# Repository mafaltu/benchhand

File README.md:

<!-- SPDX-License-Identifier: CC-BY-SA-4.0 -->
<!-- Copyright (c) 2026 Martin Faltus (mafaltu) -->

<h1 align="center">BenchHand</h1>

<p align="center"><b>Remote hands for your test bench</b><br>
Press buttons, flip switches, power-cycle boards, unplug USB and read signals from a script, a CI job or an AI agent.</p>

<p align="center">

</p>

---

## What is it?

BenchHand is a small USB box that sits between your computer and the hardware you are developing. It gives the
computer what it has always lacked on a test bench: **hands and eyes**.

- **5 relays** (potential-free contacts NC / COM / NO) can do anything a hand or a switch would. They press any button
  on the device, stand in for a switch, power-cycle a small board, apply a voltage to an input, or set a jumper or strap
  pin. They are signal relays (1 A at up to 30 V DC), made for low-voltage bench signals, not for mains or heavy loads.
- **A switched USB 2.0 passthrough** (480 Mbit/s) unplugs and replugs a USB device or programmer in software, power and
  data, with no hand on the cable.
- **4 isolated digital inputs** (3-12 V) are the eyes. They watch an LED, an output pin, a status line or a power rail
  of the device under test, so you can check that it actually reacted.
- **Physical buttons and LEDs** let a human take over at any time.
- **One USB serial port** with a plain-text protocol works from any language, a shell script, a CI pipeline, or an AI
  agent that just types `HELP`.

## Why this exists

Hardware development has a dirty secret: the automation stops at the USB cable.

Your scripts can build, flash and test. Your CI can run all night. Your AI agent can debug firmware for hours. And then,
sooner or later, somebody has to **press a button**, **hold BOOT while plugging in USB**, **unplug the device and plug it
back in**, **flip a switch**, **power-cycle the target**, or **check whether that LED actually lit up**.

That somebody is a human. Humans aren't at the desk 24/7, don't answer in milliseconds, get bored of pressing the same
button for the 40th time, and occasionally go to sleep. So the whole automated pipeline sits and waits.

BenchHand removes the human from that loop, so automation can run all the way to the hardware.

## A taste of it

```text
> ID?
< OK model=BenchHand hw=r1 fw=0.1.0 proto=1 sn=005900A75943501420363441
> PULSE 1 200                         # press "reset" (relay 1) for 200 ms
< OK
> SEQ SET 2 ON; DELAY 50; SET 1 ON; DELAY 100; SET 1 OFF; DELAY 50; SET 2 OFF
< OK steps=7 delay_ms=200 async=0     # hold BOOT, tap RESET, release BOOT
> USB DISCONNECT 2000                 # unplug the USB device for 2 s, then plug it back in
< OK
> INPUT?
< OK in=0,0,0,0 rise=0,0,0,0 fall=0,0,0,0
```

What people do with it (the list is open, a relay contact plus an input can stand in for a lot):

| Use | How |
|---|---|
| **Press any button** | reset, boot, power, a menu key, a doorbell: a relay contact across the button |
| **Flip a switch** | anything that is just a contact: a door contact, a limit, reed or float switch, an on/off status line; or move an analog input between fixed points by switching resistors (e.g. a "cold" and a "hot" NTC value) |
| **Apply a signal** | switch a voltage onto an input of the device and check that the firmware notices |
| **Power-cycle** | restart a low-power board that hangs, or interrupt its supply to test brown-out recovery (signal relays: 1 A / 30 V DC max) |
| **Re-plug USB** | re-enumerate a device or programmer, test hot-plug handling, without touching the cable |
| **Watch the result** | read LEDs, output pins or rails on the isolated inputs, and count edges |
| **Close the loop** | flash an ESP32 / STM32 / RP2040, put it into its bootloader, reset it and verify it, unattended, from CI or an AI coding agent |

## Features

| | |
|---|---|
| **Control port** | USB-C, USB 2.0 Full Speed CDC ACM (no driver on Linux, macOS or Windows 10+) |
| **Relays** | 5 x SPDT (NC / COM / NO) on screw terminals, signal relays rated 1 A at up to 30 V DC (low-voltage use only, no mains), coil-state LED per relay |
| **USB passthrough** | USB-B in, USB-A out, USB 2.0 High Speed (tested at 480 Mbit/s), eFuse-protected VBUS with fault latch, software-switched data and power |
| **Inputs** | 4 x optically isolated, 3-12 V = HIGH, edge detection (`rise=` / `fall=`) |
| **Safety** | relays auto-release after `MAX_ON` (default 60 s), everything off on reset and on host sleep, watchdog |
| **Protocol** | text lines, exactly one `OK` / `ERR` reply per command, self-documenting `HELP`, sequences (`SEQ`) |
| **MCU** | STM32C071 (Cortex-M0+), crystal-less USB, firmware update over USB DFU |
| **Board** | 188.8 x 40 mm, 2 layers, all SMD on one side, designed for home assembly (stencil + hot plate / reflow) |
| **Enclosure** | 3D-printed, two parts, two-colour lid with labels (single colour works too) |

## How it works

<p align="center">
  <picture>
    <source media="(prefers-color-scheme: dark)" srcset="docs/images/block-diagram-dark.svg">
    
  </picture>
</p>

The hardware design is described in [hardware/docs](hardware/docs/README.md), and the reasons behind the main choices
are collected in [docs/design-decisions.md](docs/design-decisions.md).

## For AI agents

BenchHand is a USB device that gives a program hands on a test bench. It has 5 relays (dry contacts NC / COM / NO) to
press buttons or reset and power-cycle a device under test (DUT). It has 4 isolated digital inputs (3-12 V = HIGH) to
read DUT signals. And it has a switched USB 2.0 passthrough (USB-B in, USB-A out) to unplug and replug a programmer or
USB device. You control it with plain-text lines over a USB serial port (CDC ACM).

**Port.**
- Linux: `/dev/serial/by-id/usb-mafaltu_BenchHand_<serial>-if00`.
- macOS: `/dev/cu.usbmodem*` (not tested).
- Windows: a `COMn` port, USB ID `1209:0001` (not tested). Match on the name `BenchHand`, not on the PID.

If several boards are connected, ask the user which one to use, and match the `sn=` field of `ID?`.

**Open.**
- Linux shell: run `stty -F <port> raw -echo` first.
- Python: use `serial.Serial(port, timeout=1)`. Baud rate, parity and DTR / RTS are ignored.
- Only one program at a time. Use `flock <port> <cmd>` if several programs may open the port.

**Protocol.**
- One command per line (LF, CR or CRLF), at most 320 characters, case-insensitive, channels by number (relays 1-5,
  inputs 1-4).
- Exactly one reply per command, in order: zero or more data lines starting with `# `, then one final line starting
  with `OK` or `ERR`. Read until that final line.
- Errors look like `ERR <code> <reason>: <hint>`, and the hint says how to fix the call.
- `HELP` lists the commands, and `HELP <command>` gives details and examples.

**Rules you must respect.**
1. **Ask what is wired.** The board does not know what a relay or input is connected to. Ask the user (e.g. "relay 1 =
   DUT reset to GND, input 1 = status LED") and use only those channels.
2. **Relays switch real circuits.** Never switch a relay you were not told about. A relay switched ON from the port
   turns OFF by itself after `MAX_ON` (60 s by default). Send `SET <n> ON` again as a keep-alive. Change `MAX_ON` only
   if the user agrees.
3. **After a board reset everything is off**, except the USB passthrough, which comes back ON.
4. **Host sleep turns everything off.** So does Linux USB autosuspend while no program has the port open. Keep the
   port open or ask the user about the udev rule in the [firmware README](firmware/README.md).
5. **Unplugging through the passthrough is not a safe eject.** Unmount mass-storage devices first.
6. **`ext=1` in `STATUS?`** means foreign voltage is present on the USB-A output. Tell the user.
7. **Inputs take 3-12 V.** Never ask the user to connect more than 12 V.
8. **`REBOOT` / `BOOTLOADER`** reply `OK` and then drop the port. Re-open it after about 1 s. Use `BOOTLOADER` (USB DFU
   firmware update) only when asked.

Minimal Python client:

```python
import glob, serial
port = glob.glob("/dev/serial/by-id/usb-mafaltu_BenchHand_*-if00")[0]
p = serial.Serial(port, timeout=1)

def cmd(line):
    p.write((line + "\n").encode())
    reply = []
    while True:
        l = p.readline().decode().rstrip("\r\n")
        reply.append(l)
        if l.startswith(("OK", "ERR")):
            return reply

print(cmd("ID?"))
print(cmd("HELP"))
```

The full agent guide, including the table of all commands of the current protocol version, is
[firmware/docs/agent_quickstart.md](firmware/docs/agent_quickstart.md). The complete reference is
[firmware/docs/PROTOCOL.md](firmware/docs/PROTOCOL.md), and the board's own `HELP` is authoritative.

## Build your own

| Step | What | Where |
|---|---|---|
| 1. PCB | Order the 2-layer board from the Gerbers (any standard prototype fab) | [hardware/fabrication](hardware/fabrication/) |
| 2. Parts | Universal BOM: key specs, substitutes, Mouser / DigiKey / TME / LCSC codes | [hardware/bom](hardware/bom/README.md) |
| 3. Assembly | Stencil + reflow for the SMD side, then the through-hole parts | [assembly notes](hardware/fabrication/benchhand-r1-assembly-notes.md) |
| 4. Firmware | Build with CMake + arm-none-eabi-gcc, flash over SWD once (generic Tag-Connect TC2050 cable, custom pinout: [adapter wiring](hardware/docs/README.md#adapter-wiring)), then over USB DFU | [firmware](firmware/README.md) |
| 5. Enclosure | Print the two parts (generic 3MF / STEP), insert 4 screws | [enclosure](enclosure/PRINTING.md) |

## Repository layout

```text
hardware/   KiCad 10 project, fabrication files, BOM, hardware docs and known issues
firmware/   STM32C071 firmware (TinyUSB, ST HAL), protocol, agent guide
enclosure/  parametric CadQuery enclosure, print-ready 3MF / STEP, print guide, renders
docs/       design decisions
```

Clone with submodules: `git clone --recurse-submodules https://github.com/mafaltu/benchhand`

## How this was made

**Short version: AI built it. I dreamed it.**

AI agents (Claude Code and OpenAI Codex) generated every schematic symbol, every copper trace, every line of firmware,
every design review, every page of documentation and every curve of the 3D-printed enclosure in this repository. Yes, this README
too.

I'm the spiritual leader of the operation. The idea, the vision of what a bench tool like this should be, and the
direction of the project are mine. I led the AI the way an experienced developer leads a team, and it did the rest.
The one thing it didn't do is solder the board. *Yet.*

It was also an experiment: how far can AI take a complete hardware product, from an idea to a working device on the
bench? Pretty far, it turns out.

**It isn't perfect.** Revision 1 works, but I'd do a few things differently next time. See
[known issues](hardware/docs/known-issues.md). Found something else? Open an issue.

## Licence

BenchHand is open source hardware. You may build it, change it and sell it. If you distribute a modified version,
you must publish your changes under the same licence and credit the original project.

| Part | Licence |
|---|---|
| Hardware (`hardware/`) | [CERN-OHL-S-2.0](hardware/LICENSE) |
| Firmware (`firmware/`) | [GPL-3.0-or-later](firmware/LICENSE). Bundled libraries keep their own licences (TinyUSB MIT, ST HAL BSD-3-Clause, CMSIS Apache-2.0). |
| Enclosure, docs, images | [CC BY-SA 4.0](enclosure/LICENSE) |

"BenchHand" is the name of this project. Clones and derivatives are welcome, but please don't sell them under the
name BenchHand.

Copyright (c) 2026 Martin Faltus (mafaltu)

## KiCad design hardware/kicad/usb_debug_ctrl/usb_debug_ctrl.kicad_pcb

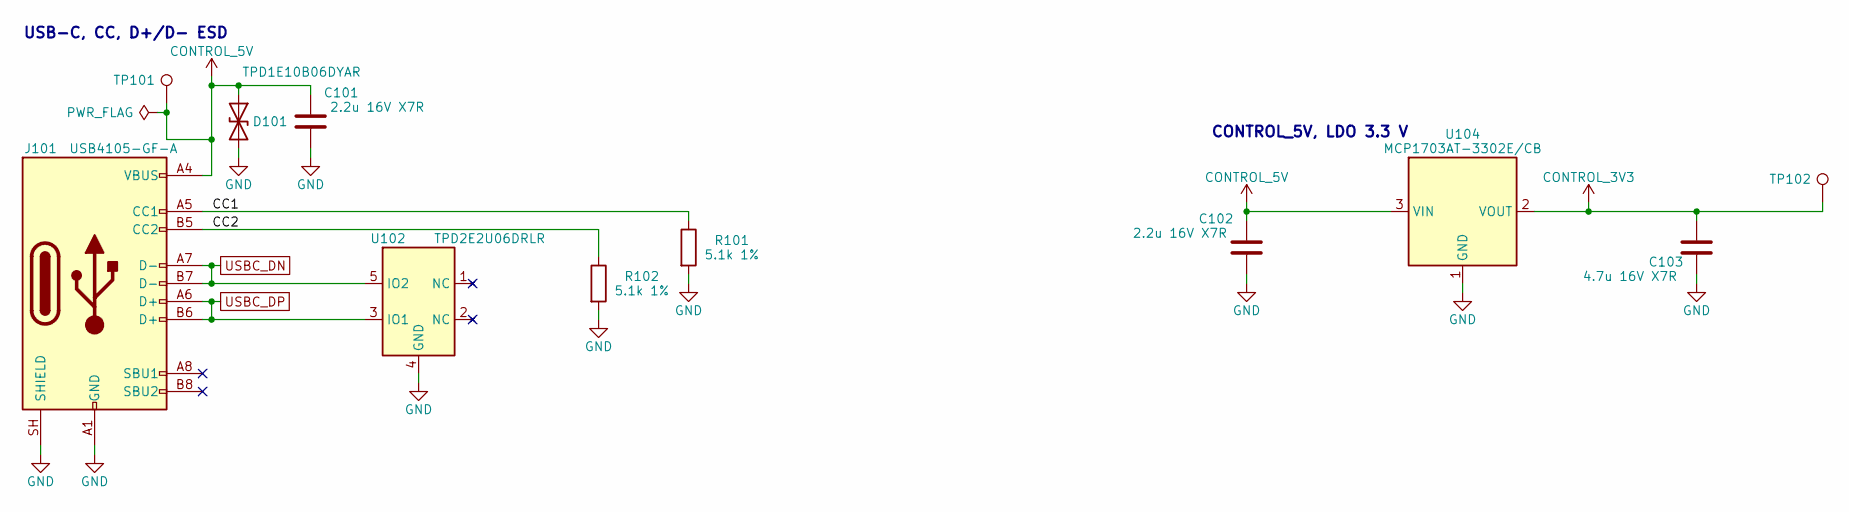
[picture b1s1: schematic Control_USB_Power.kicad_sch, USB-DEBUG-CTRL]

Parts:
C101, C102: 2.2u 16V X7R; C_0805_2012Metric; MPN CC0805KKX7R7BB225
C103: 4.7u 16V X7R; C_0805_2012Metric; MPN CL21B475KOFNNNE
D101: TPD1E10B06DYAR; D_SOD-523; MPN TPD1E10B06DYAR
J101: USB4105-GF-A; USB_C_Receptacle_GCT_USB4105-xx-A_16P_TopMnt_Horizontal; MPN USB4105-GF-A
R101, R102: 5.1k 1%; R_0603_1608Metric; MPN RC0603FR-075K1L
TP101, TP102: test pad 1.0 mm; TestPoint_Pad_D1.0mm; MPN none (copper only)
U102: TPD2E2U06DRLR; Texas_R-PDSO-N5_DRL-5_usb_relay; MPN TPD2E2U06DRLR
U104: MCP1703AT-3302E/CB; SOT-23; MPN MCP1703AT-3302E/CB

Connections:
/Control_USB_Power/CC1: J101.A5 (CC1), R101.1
/Control_USB_Power/CC2: J101.B5 (CC2), R102.1
CONTROL_3V3: C103.1, TP102.1, U104.2 (VOUT); also elsewhere on the board
CONTROL_5V: C101.1, C102.1, D101.1 (A1), J101.A4 (VBUS), J101.A9 (VBUS), J101.B4 (VBUS), J101.B9 (VBUS), TP101.1, U104.3 (VIN); also elsewhere on the board
GND: C101.2, C102.2, C103.2, D101.2 (A2), J101.A1 (GND), J101.A12 (GND), J101.B1 (GND), J101.B12 (GND), J101.SH (SHIELD), R101.2, R102.2, U102.4 (GND), U104.1 (GND); also elsewhere on the board
USBC_DN: J101.A7 (D-), J101.B7 (D-), U102.5 (IO2); also elsewhere on the board
USBC_DP: J101.A6 (D+), J101.B6 (D+), U102.3 (IO1); also elsewhere on the board

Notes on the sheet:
USB-C, CC, D+/D- ESD
CONTROL_5V, LDO 3.3 V

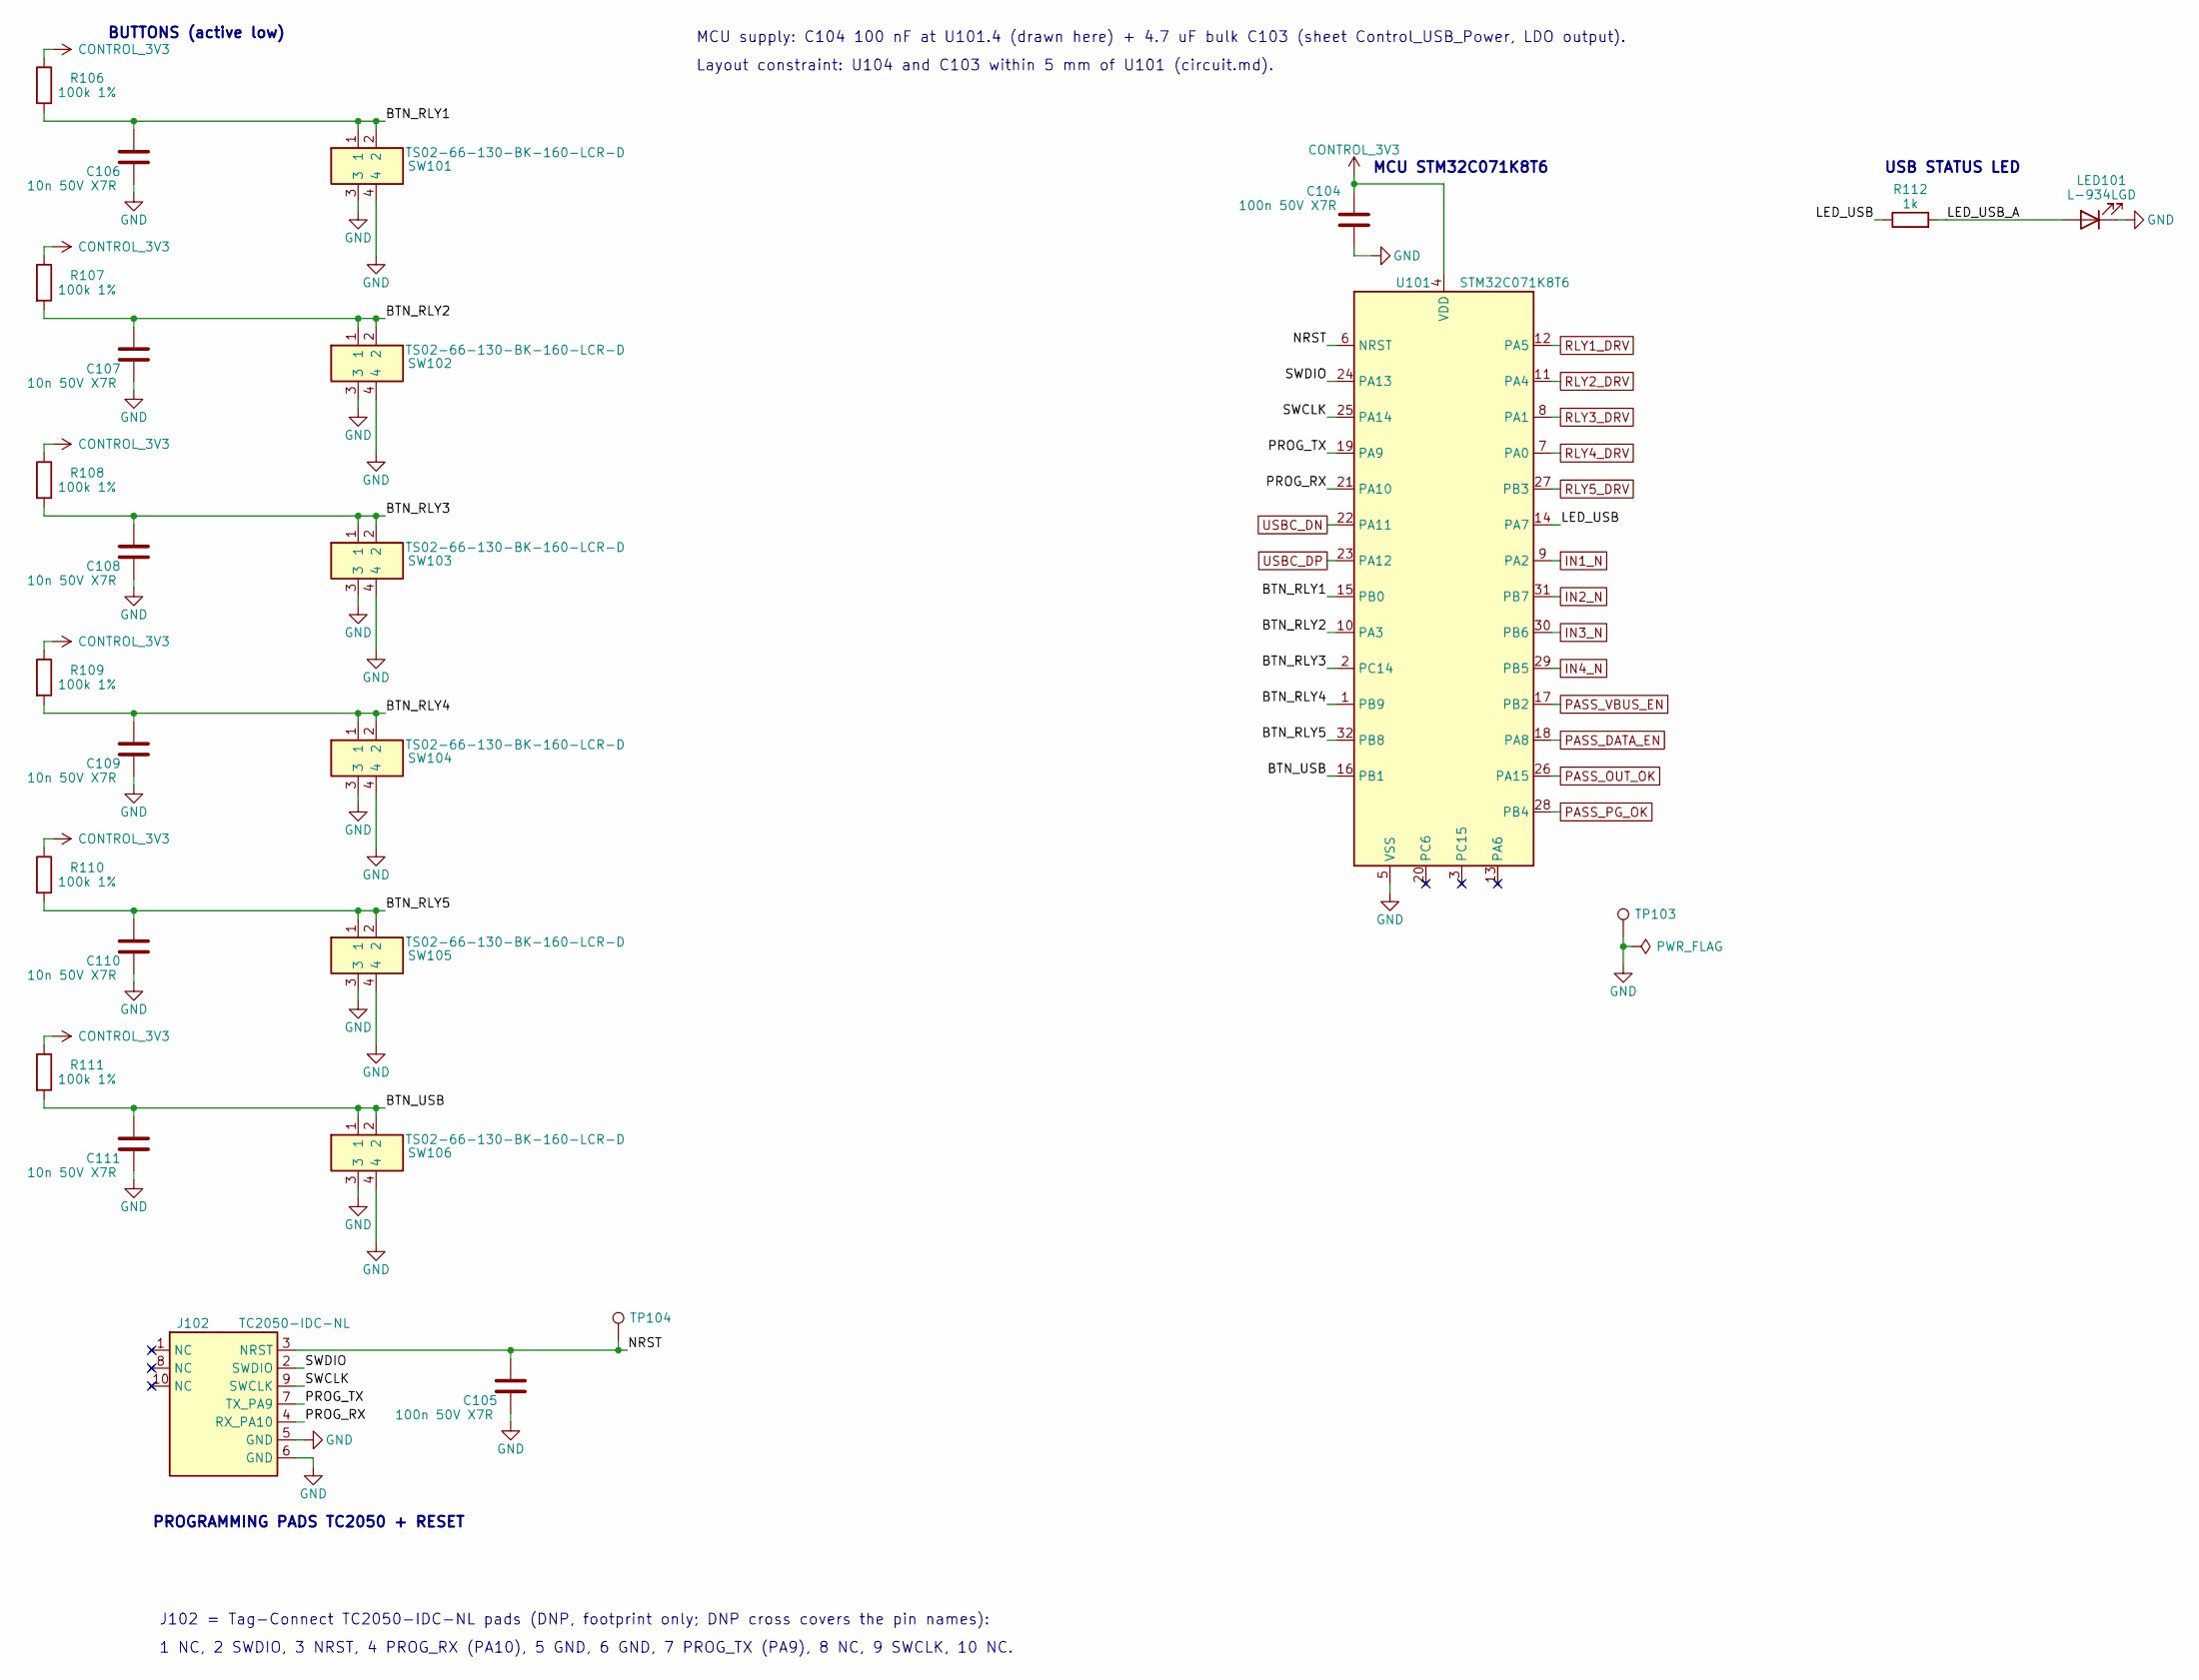
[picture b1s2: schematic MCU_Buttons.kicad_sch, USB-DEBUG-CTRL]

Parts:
C104, C105: 100n 50V X7R; C_0603_1608Metric; MPN CC0603KRX7R9BB104
C106, C107, C108, C109, C110, C111: 10n 50V X7R; C_0603_1608Metric; MPN CC0603KRX7R9BB103
J102: TC2050-IDC-NL; Tag-Connect_TC2050-IDC-NL_2x05_P1.27mm_Vertical_usb_relay; MPN none (PCB footprint only)
LED101: L-934LGD; LED_D3.0mm_AK_usb_relay; MPN L-934LGD
R106, R107, R108, R109, R110, R111: 100k 1%; R_0603_1608Metric; MPN RC0603FR-07100KL
R112: 1k; R_0603_1608Metric; MPN RC0603FR-071KL
SW101, SW102, SW103, SW104, SW105, SW106: TS02-66-130-BK-160-LCR-D; SW_PUSH_6mm_H13mm_usb_relay; MPN TS02-66-130-BK-160-LCR-D
TP103, TP104: test pad 1.0 mm; TestPoint_Pad_D1.0mm; MPN none (copper only)
U101: STM32C071K8T6; LQFP-32_7x7mm_P0.8mm; MPN STM32C071K8T6

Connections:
/MCU_Buttons/BTN_RLY1: C106.1, R106.2, SW101.1, SW101.2, U101.15 (PB0)
/MCU_Buttons/BTN_RLY2: C107.1, R107.2, SW102.1, SW102.2, U101.10 (PA3)
/MCU_Buttons/BTN_RLY3: C108.1, R108.2, SW103.1, SW103.2, U101.2 (PC14)
/MCU_Buttons/BTN_RLY4: C109.1, R109.2, SW104.1, SW104.2, U101.1 (PB9)
/MCU_Buttons/BTN_RLY5: C110.1, R110.2, SW105.1, SW105.2, U101.32 (PB8)
/MCU_Buttons/BTN_USB: C111.1, R111.2, SW106.1, SW106.2, U101.16 (PB1)
/MCU_Buttons/LED_USB: R112.1, U101.14 (PA7)
/MCU_Buttons/LED_USB_A: LED101.A, R112.2
/MCU_Buttons/NRST: C105.1, J102.3 (NRST), TP104.1, U101.6 (NRST)
/MCU_Buttons/PROG_RX: J102.4 (RX_PA10), U101.21 (PA10)
/MCU_Buttons/PROG_TX: J102.7 (TX_PA9), U101.19 (PA9)
/MCU_Buttons/SWCLK: J102.9 (SWCLK), U101.25 (PA14)
/MCU_Buttons/SWDIO: J102.2 (SWDIO), U101.24 (PA13)
CONTROL_3V3: C104.1, R106.1, R107.1, R108.1, R109.1, R110.1, R111.1, U101.4 (VDD); also elsewhere on the board
GND: C104.2, C105.2, C106.2, C107.2, C108.2, C109.2, C110.2, C111.2, J102.5 (GND), J102.6 (GND), LED101.K, SW101.3, SW101.4, SW102.3, SW102.4, SW103.3, SW103.4, SW104.3, SW104.4, SW105.3, SW105.4, SW106.3, SW106.4, TP103.1, U101.5 (VSS); also elsewhere on the board
IN1_N: U101.9 (PA2); also elsewhere on the board
IN2_N: U101.31 (PB7); also elsewhere on the board
IN3_N: U101.30 (PB6); also elsewhere on the board
IN4_N: U101.29 (PB5); also elsewhere on the board
PASS_DATA_EN: U101.18 (PA8); also elsewhere on the board
PASS_OUT_OK: U101.26 (PA15); also elsewhere on the board
PASS_PG_OK: U101.28 (PB4); also elsewhere on the board
PASS_VBUS_EN: U101.17 (PB2); also elsewhere on the board
RLY1_DRV: U101.12 (PA5); also elsewhere on the board
RLY2_DRV: U101.11 (PA4); also elsewhere on the board
RLY3_DRV: U101.8 (PA1); also elsewhere on the board
RLY4_DRV: U101.7 (PA0); also elsewhere on the board
RLY5_DRV: U101.27 (PB3); also elsewhere on the board
USBC_DN: U101.22 (PA11); also elsewhere on the board
USBC_DP: U101.23 (PA12); also elsewhere on the board

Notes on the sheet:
BUTTONS (active low)
PROGRAMMING PADS TC2050 + RESET
MCU STM32C071K8T6
USB STATUS LED
MCU supply: C104 100 nF at U101.4 (drawn here) + 4.7 uF bulk C103 (sheet Control_USB_Power, LDO output).
Layout constraint: U104 and C103 within 5 mm of U101 (circuit.md).
J102 = Tag-Connect TC2050-IDC-NL pads (DNP, footprint only; DNP cross covers the pin names):
1 NC, 2 SWDIO, 3 NRST, 4 PROG_RX (PA10), 5 GND, 6 GND, 7 PROG_TX (PA9), 8 NC, 9 SWCLK, 10 NC.

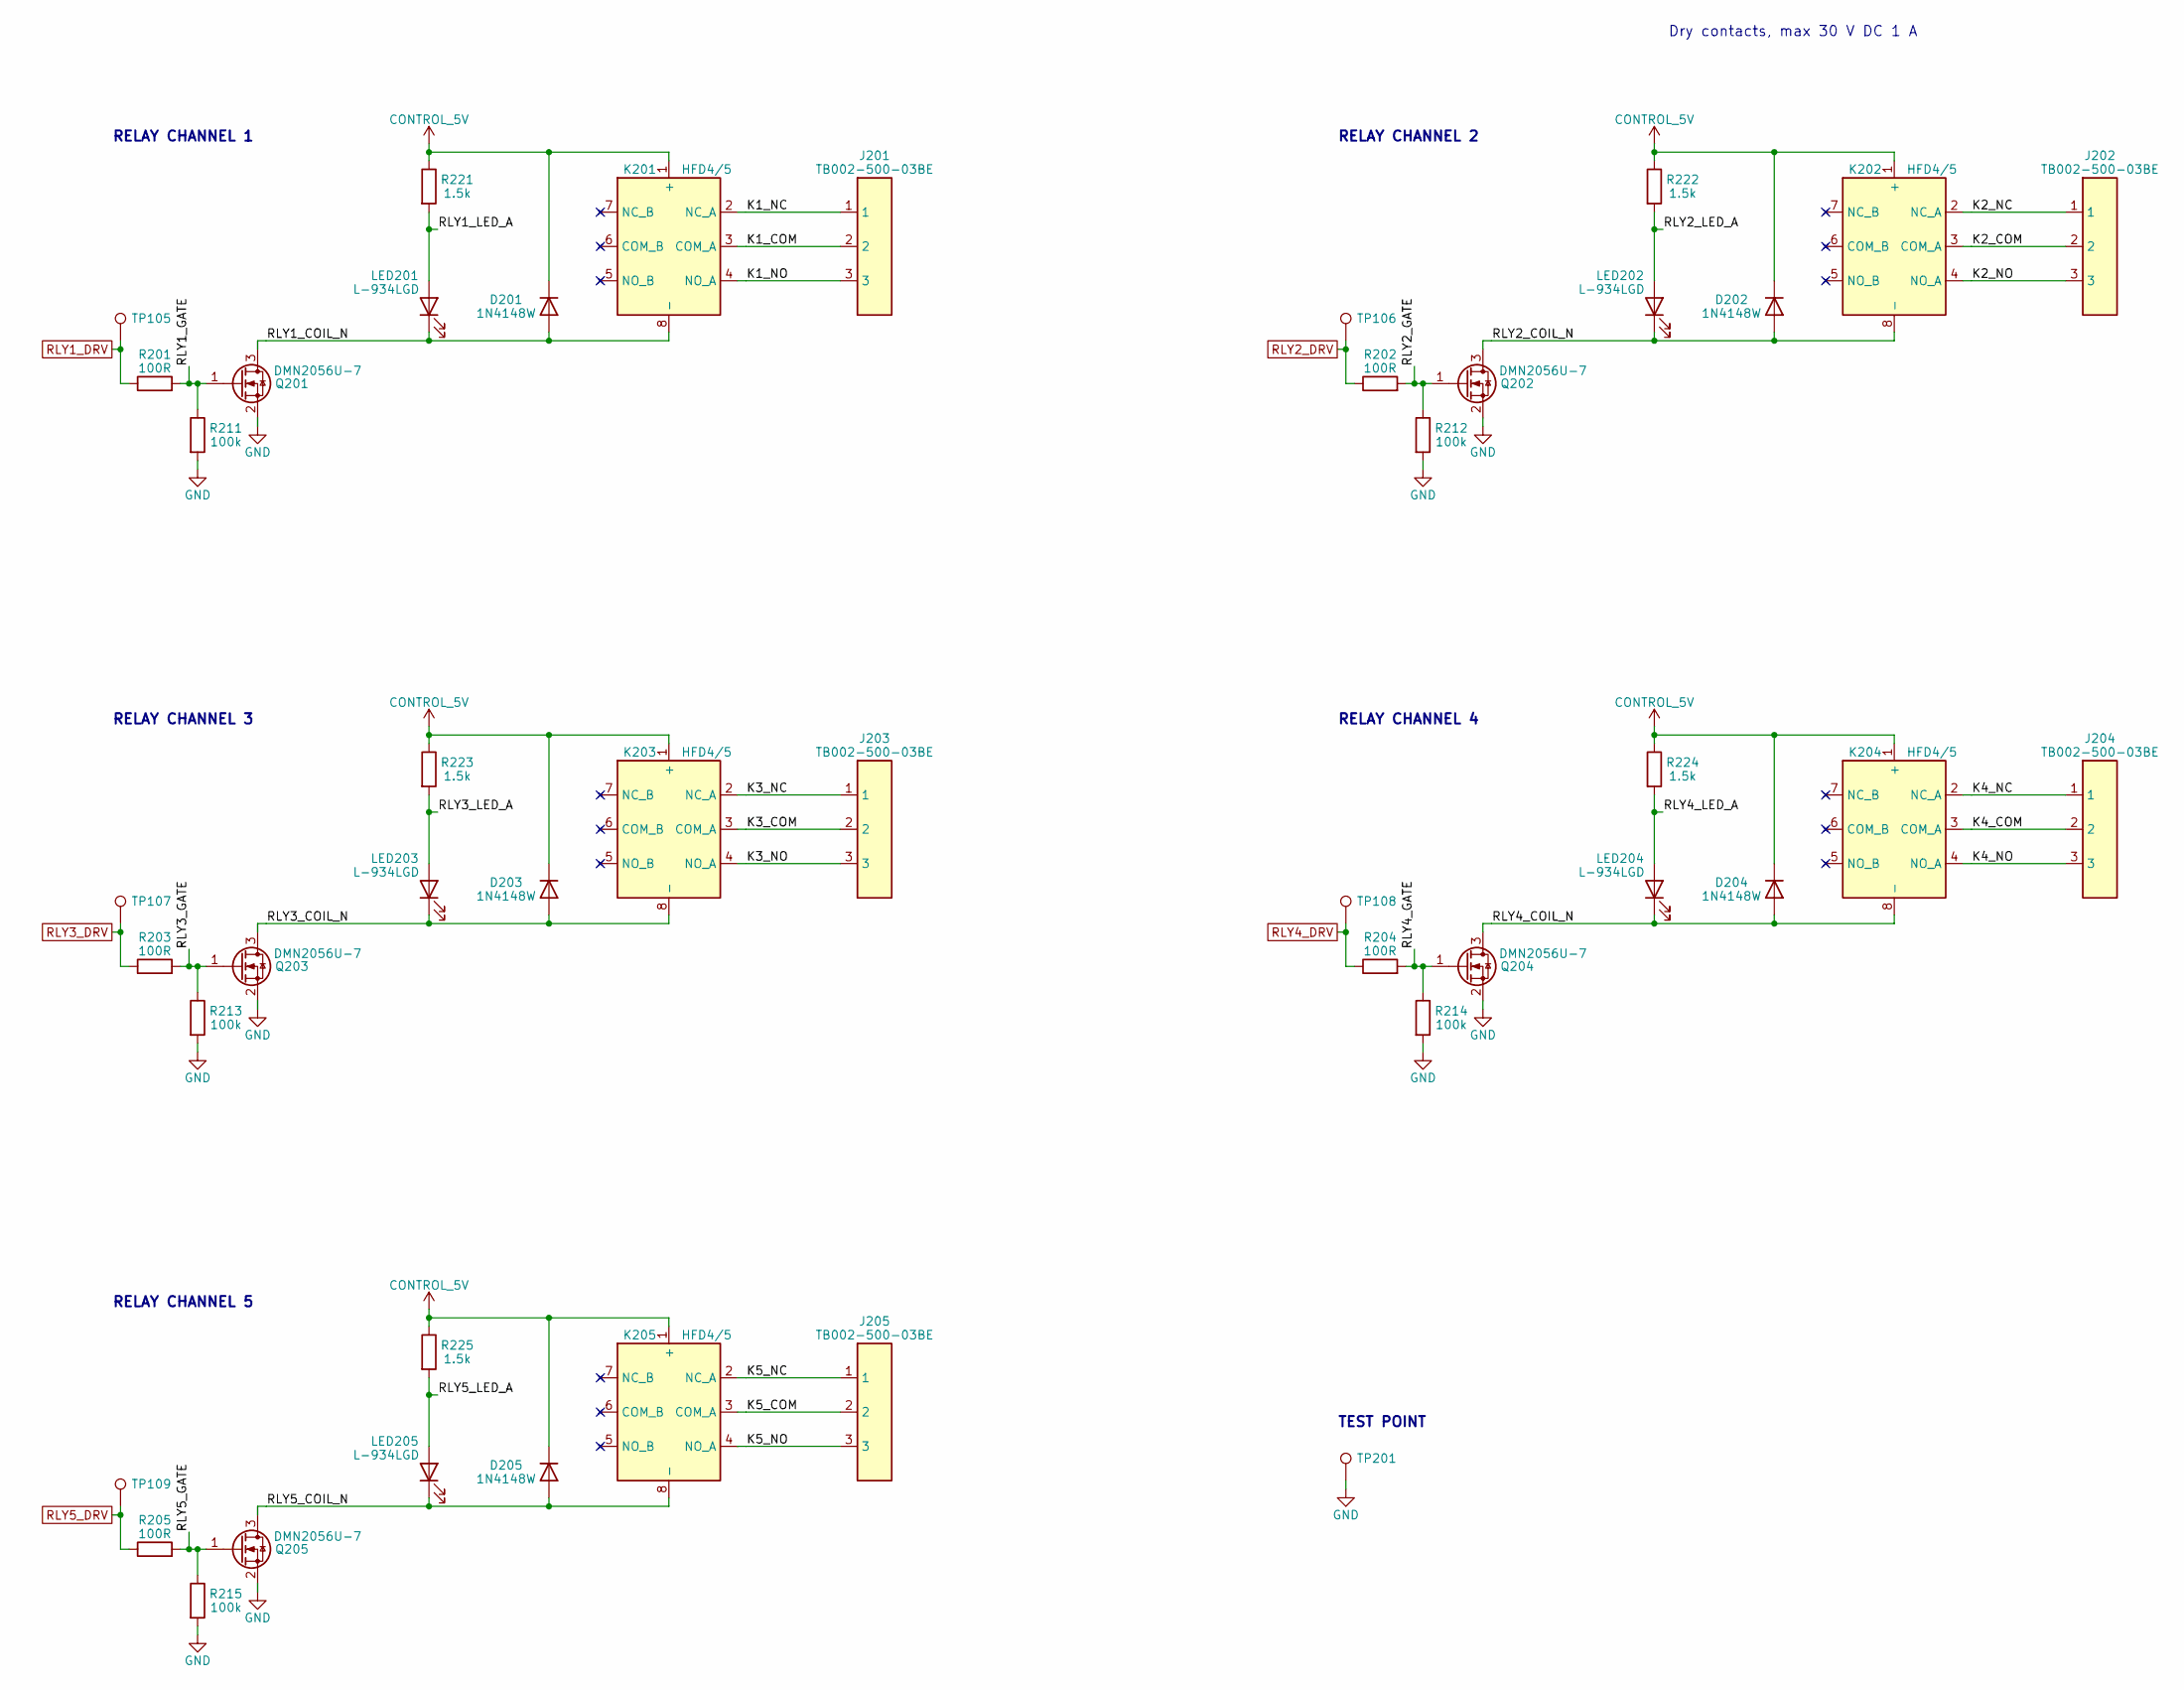
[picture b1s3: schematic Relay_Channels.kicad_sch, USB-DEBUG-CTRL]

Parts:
D201, D202, D203, D204, D205: 1N4148W; D_SOD-123; MPN 1N4148W
J201, J202, J203, J204, J205: TB002-500-03BE; TerminalBlock_SameSky_TB002-500-03BE_1x03_P5.00mm_Horizontal; MPN TB002-500-03BE
K201, K202, K203, K204, K205: HFD4/5; Relay_THT_Hongfa_HFD4; MPN HFD4/5
LED201, LED202, LED203, LED204, LED205: L-934LGD; LED_D3.0mm; MPN L-934LGD
Q201, Q202, Q203, Q204, Q205: DMN2056U-7; SOT-23; MPN DMN2056U-7
R201, R202, R203, R204, R205: 100R; R_0603_1608Metric; MPN RC0603FR-07100RL
R211, R212, R213, R214, R215: 100k; R_0603_1608Metric; MPN RC0603FR-07100KL
R221, R222, R223, R224, R225: 1.5k; R_0603_1608Metric; MPN RC0603FR-071K5L
TP105, TP106, TP107, TP108, TP109, TP201: test pad 1.0 mm; TestPoint_Pad_D1.0mm; MPN none (copper only)

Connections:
/Relay_Channels/K1_COM: J201.2, K201.3 (COM_A)
/Relay_Channels/K1_NC: J201.1, K201.2 (NC_A)
/Relay_Channels/K1_NO: J201.3, K201.4 (NO_A)
/Relay_Channels/K2_COM: J202.2, K202.3 (COM_A)
/Relay_Channels/K2_NC: J202.1, K202.2 (NC_A)
/Relay_Channels/K2_NO: J202.3, K202.4 (NO_A)
/Relay_Channels/K3_COM: J203.2, K203.3 (COM_A)
/Relay_Channels/K3_NC: J203.1, K203.2 (NC_A)
/Relay_Channels/K3_NO: J203.3, K203.4 (NO_A)
/Relay_Channels/K4_COM: J204.2, K204.3 (COM_A)
/Relay_Channels/K4_NC: J204.1, K204.2 (NC_A)
/Relay_Channels/K4_NO: J204.3, K204.4 (NO_A)
/Relay_Channels/K5_COM: J205.2, K205.3 (COM_A)
/Relay_Channels/K5_NC: J205.1, K205.2 (NC_A)
/Relay_Channels/K5_NO: J205.3, K205.4 (NO_A)
/Relay_Channels/RLY1_COIL_N: D201.2 (A), K201.8 (-), LED201.1 (K), Q201.3 (D)
/Relay_Channels/RLY1_GATE: Q201.1 (G), R201.2, R211.1
/Relay_Channels/RLY1_LED_A: LED201.2 (A), R221.2
/Relay_Channels/RLY2_COIL_N: D202.2 (A), K202.8 (-), LED202.1 (K), Q202.3 (D)
/Relay_Channels/RLY2_GATE: Q202.1 (G), R202.2, R212.1
/Relay_Channels/RLY2_LED_A: LED202.2 (A), R222.2
/Relay_Channels/RLY3_COIL_N: D203.2 (A), K203.8 (-), LED203.1 (K), Q203.3 (D)
/Relay_Channels/RLY3_GATE: Q203.1 (G), R203.2, R213.1
/Relay_Channels/RLY3_LED_A: LED203.2 (A), R223.2
/Relay_Channels/RLY4_COIL_N: D204.2 (A), K204.8 (-), LED204.1 (K), Q204.3 (D)
/Relay_Channels/RLY4_GATE: Q204.1 (G), R204.2, R214.1
/Relay_Channels/RLY4_LED_A: LED204.2 (A), R224.2
/Relay_Channels/RLY5_COIL_N: D205.2 (A), K205.8 (-), LED205.1 (K), Q205.3 (D)
/Relay_Channels/RLY5_GATE: Q205.1 (G), R205.2, R215.1
/Relay_Channels/RLY5_LED_A: LED205.2 (A), R225.2
CONTROL_5V: D201.1 (K), D202.1 (K), D203.1 (K), D204.1 (K), D205.1 (K), K201.1 (+), K202.1 (+), K203.1 (+), K204.1 (+), K205.1 (+), R221.1, R222.1, R223.1, R224.1, R225.1; also elsewhere on the board
GND: Q201.2 (S), Q202.2 (S), Q203.2 (S), Q204.2 (S), Q205.2 (S), R211.2, R212.2, R213.2, R214.2, R215.2, TP201.1; also elsewhere on the board
RLY1_DRV: R201.1, TP105.1; also elsewhere on the board
RLY2_DRV: R202.1, TP106.1; also elsewhere on the board
RLY3_DRV: R203.1, TP107.1; also elsewhere on the board
RLY4_DRV: R204.1, TP108.1; also elsewhere on the board
RLY5_DRV: R205.1, TP109.1; also elsewhere on the board

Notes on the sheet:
RELAY CHANNEL 1
RELAY CHANNEL 2
RELAY CHANNEL 3
RELAY CHANNEL 4
RELAY CHANNEL 5
TEST POINT
Dry contacts, max 30 V DC 1 A

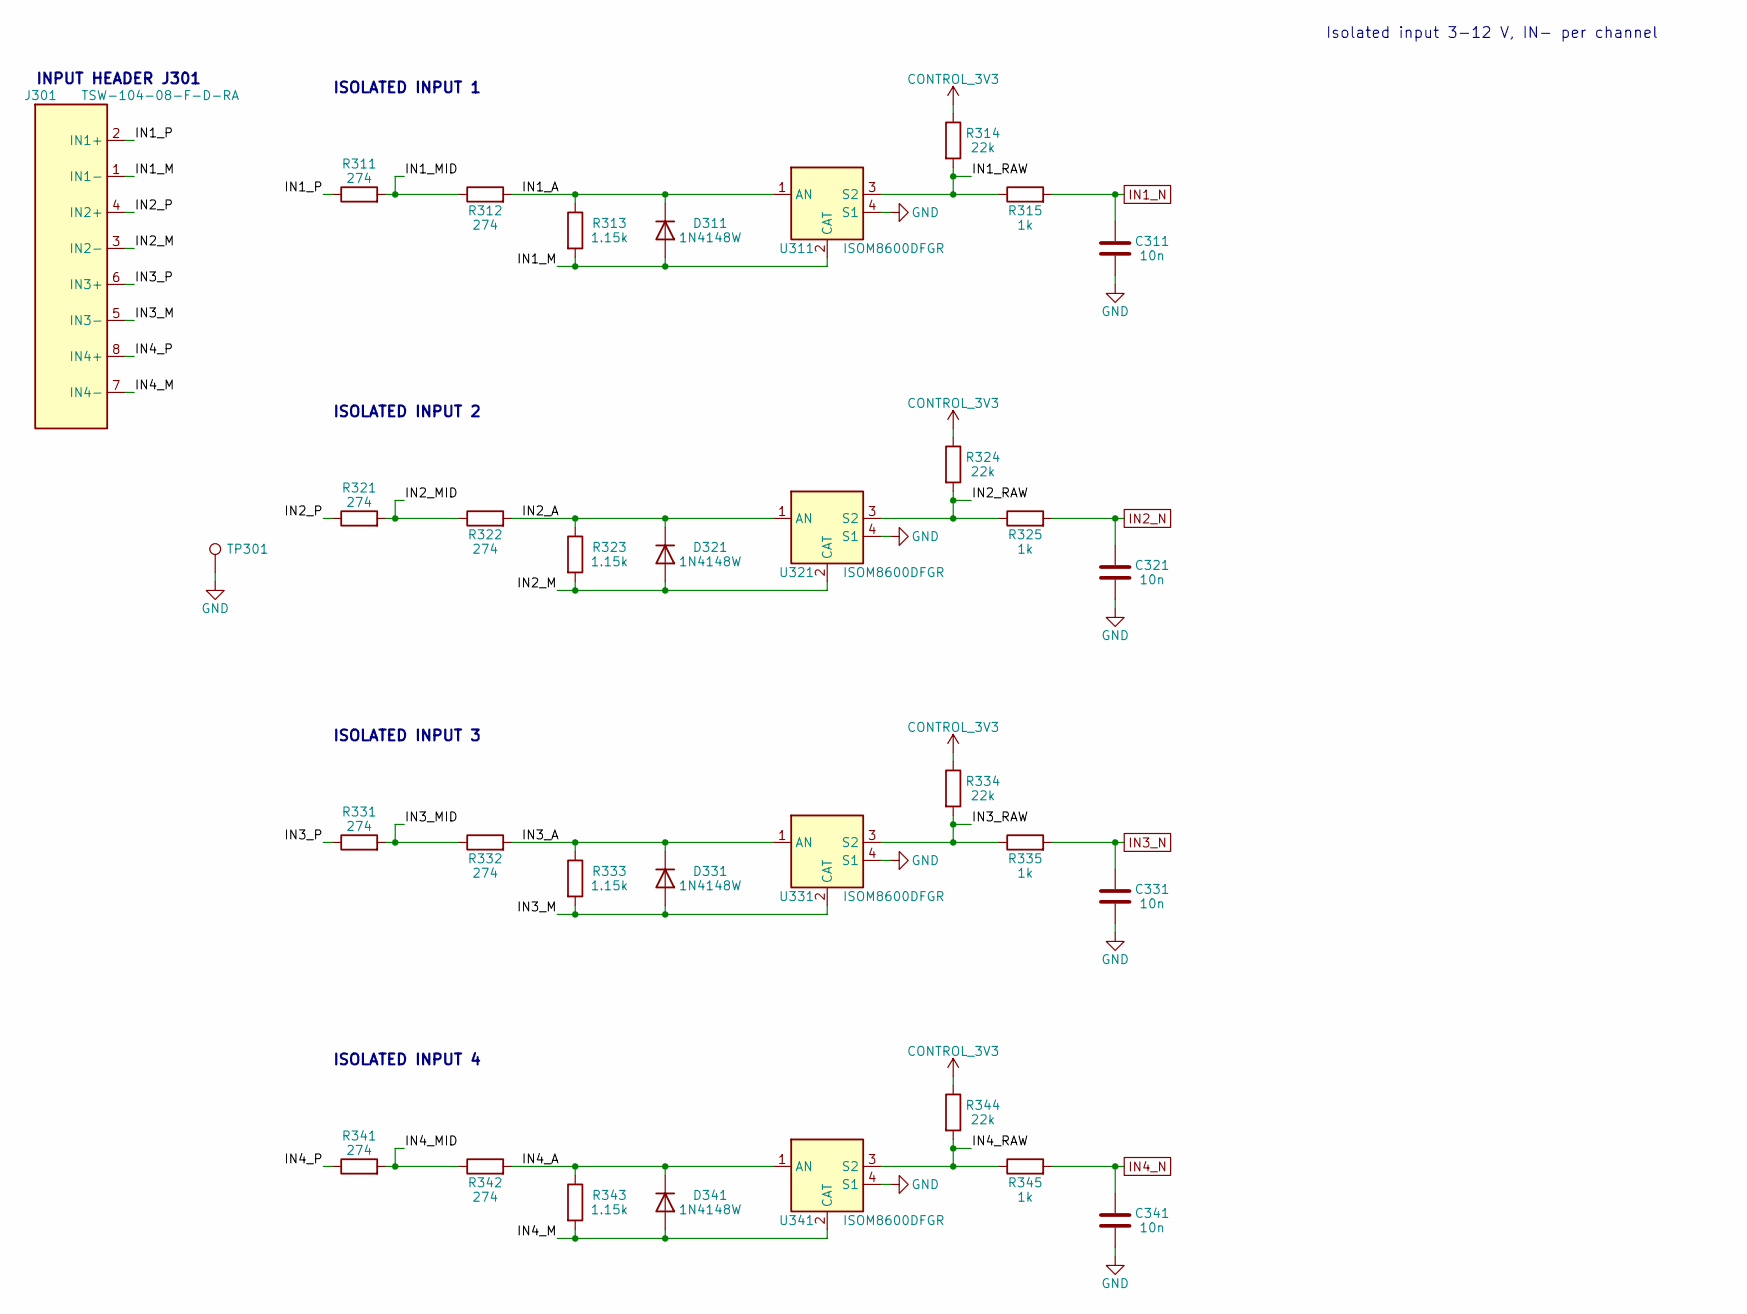
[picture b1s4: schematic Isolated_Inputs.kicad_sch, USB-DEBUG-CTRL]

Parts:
C311, C321, C331, C341: 10n; C_0603_1608Metric; MPN CC0603KRX7R9BB103
D311, D321, D331, D341: 1N4148W; D_SOD-123; MPN 1N4148W
J301: TSW-104-08-F-D-RA; PinHeader_2x04_P2.54mm_Horizontal_usb_relay; MPN TSW-104-08-F-D-RA
R311, R312, R321, R322, R331, R332, R341, R342: 274; R_1206_3216Metric; MPN RC1206FR-07274RL
R313, R323, R333, R343: 1.15k; R_0603_1608Metric; MPN RC0603FR-071K15L
R314, R324, R334, R344: 22k; R_0603_1608Metric; MPN RC0603FR-0722KL
R315, R325, R335, R345: 1k; R_0603_1608Metric; MPN RC0603FR-071KL
TP301: test pad 1.0 mm; TestPoint_Pad_D1.0mm; MPN none (copper only)
U311, U321, U331, U341: ISOM8600DFGR; SO-4_4.4x3.6mm_P2.54mm_usb_relay; MPN ISOM8600DFGR

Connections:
/Isolated_Inputs/IN1_A: D311.1 (K), R312.2, R313.1, U311.1 (AN)
/Isolated_Inputs/IN1_M: D311.2 (A), J301.1 (IN1-), R313.2, U311.2 (CAT)
/Isolated_Inputs/IN1_MID: R311.2, R312.1
/Isolated_Inputs/IN1_P: J301.2 (IN1+), R311.1
/Isolated_Inputs/IN1_RAW: R314.2, R315.1, U311.3 (S2)
/Isolated_Inputs/IN2_A: D321.1 (K), R322.2, R323.1, U321.1 (AN)
/Isolated_Inputs/IN2_M: D321.2 (A), J301.3 (IN2-), R323.2, U321.2 (CAT)
/Isolated_Inputs/IN2_MID: R321.2, R322.1
/Isolated_Inputs/IN2_P: J301.4 (IN2+), R321.1
/Isolated_Inputs/IN2_RAW: R324.2, R325.1, U321.3 (S2)
/Isolated_Inputs/IN3_A: D331.1 (K), R332.2, R333.1, U331.1 (AN)
/Isolated_Inputs/IN3_M: D331.2 (A), J301.5 (IN3-), R333.2, U331.2 (CAT)
/Isolated_Inputs/IN3_MID: R331.2, R332.1
/Isolated_Inputs/IN3_P: J301.6 (IN3+), R331.1
/Isolated_Inputs/IN3_RAW: R334.2, R335.1, U331.3 (S2)
/Isolated_Inputs/IN4_A: D341.1 (K), R342.2, R343.1, U341.1 (AN)
/Isolated_Inputs/IN4_M: D341.2 (A), J301.7 (IN4-), R343.2, U341.2 (CAT)
/Isolated_Inputs/IN4_MID: R341.2, R342.1
/Isolated_Inputs/IN4_P: J301.8 (IN4+), R341.1
/Isolated_Inputs/IN4_RAW: R344.2, R345.1, U341.3 (S2)
CONTROL_3V3: R314.1, R324.1, R334.1, R344.1; also elsewhere on the board
GND: C311.2, C321.2, C331.2, C341.2, TP301.1, U311.4 (S1), U321.4 (S1), U331.4 (S1), U341.4 (S1); also elsewhere on the board
IN1_N: C311.1, R315.2; also elsewhere on the board
IN2_N: C321.1, R325.2; also elsewhere on the board
IN3_N: C331.1, R335.2; also elsewhere on the board
IN4_N: C341.1, R345.2; also elsewhere on the board

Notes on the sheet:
INPUT HEADER J301
ISOLATED INPUT 1
ISOLATED INPUT 2
ISOLATED INPUT 3
ISOLATED INPUT 4
Isolated input 3-12 V, IN- per channel

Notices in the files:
README.md:
Hardware licence CERN-OHL-S-2.0
Firmware licence GPL-3.0-or-later
Enclosure and docs licence CC BY-SA 4.0
